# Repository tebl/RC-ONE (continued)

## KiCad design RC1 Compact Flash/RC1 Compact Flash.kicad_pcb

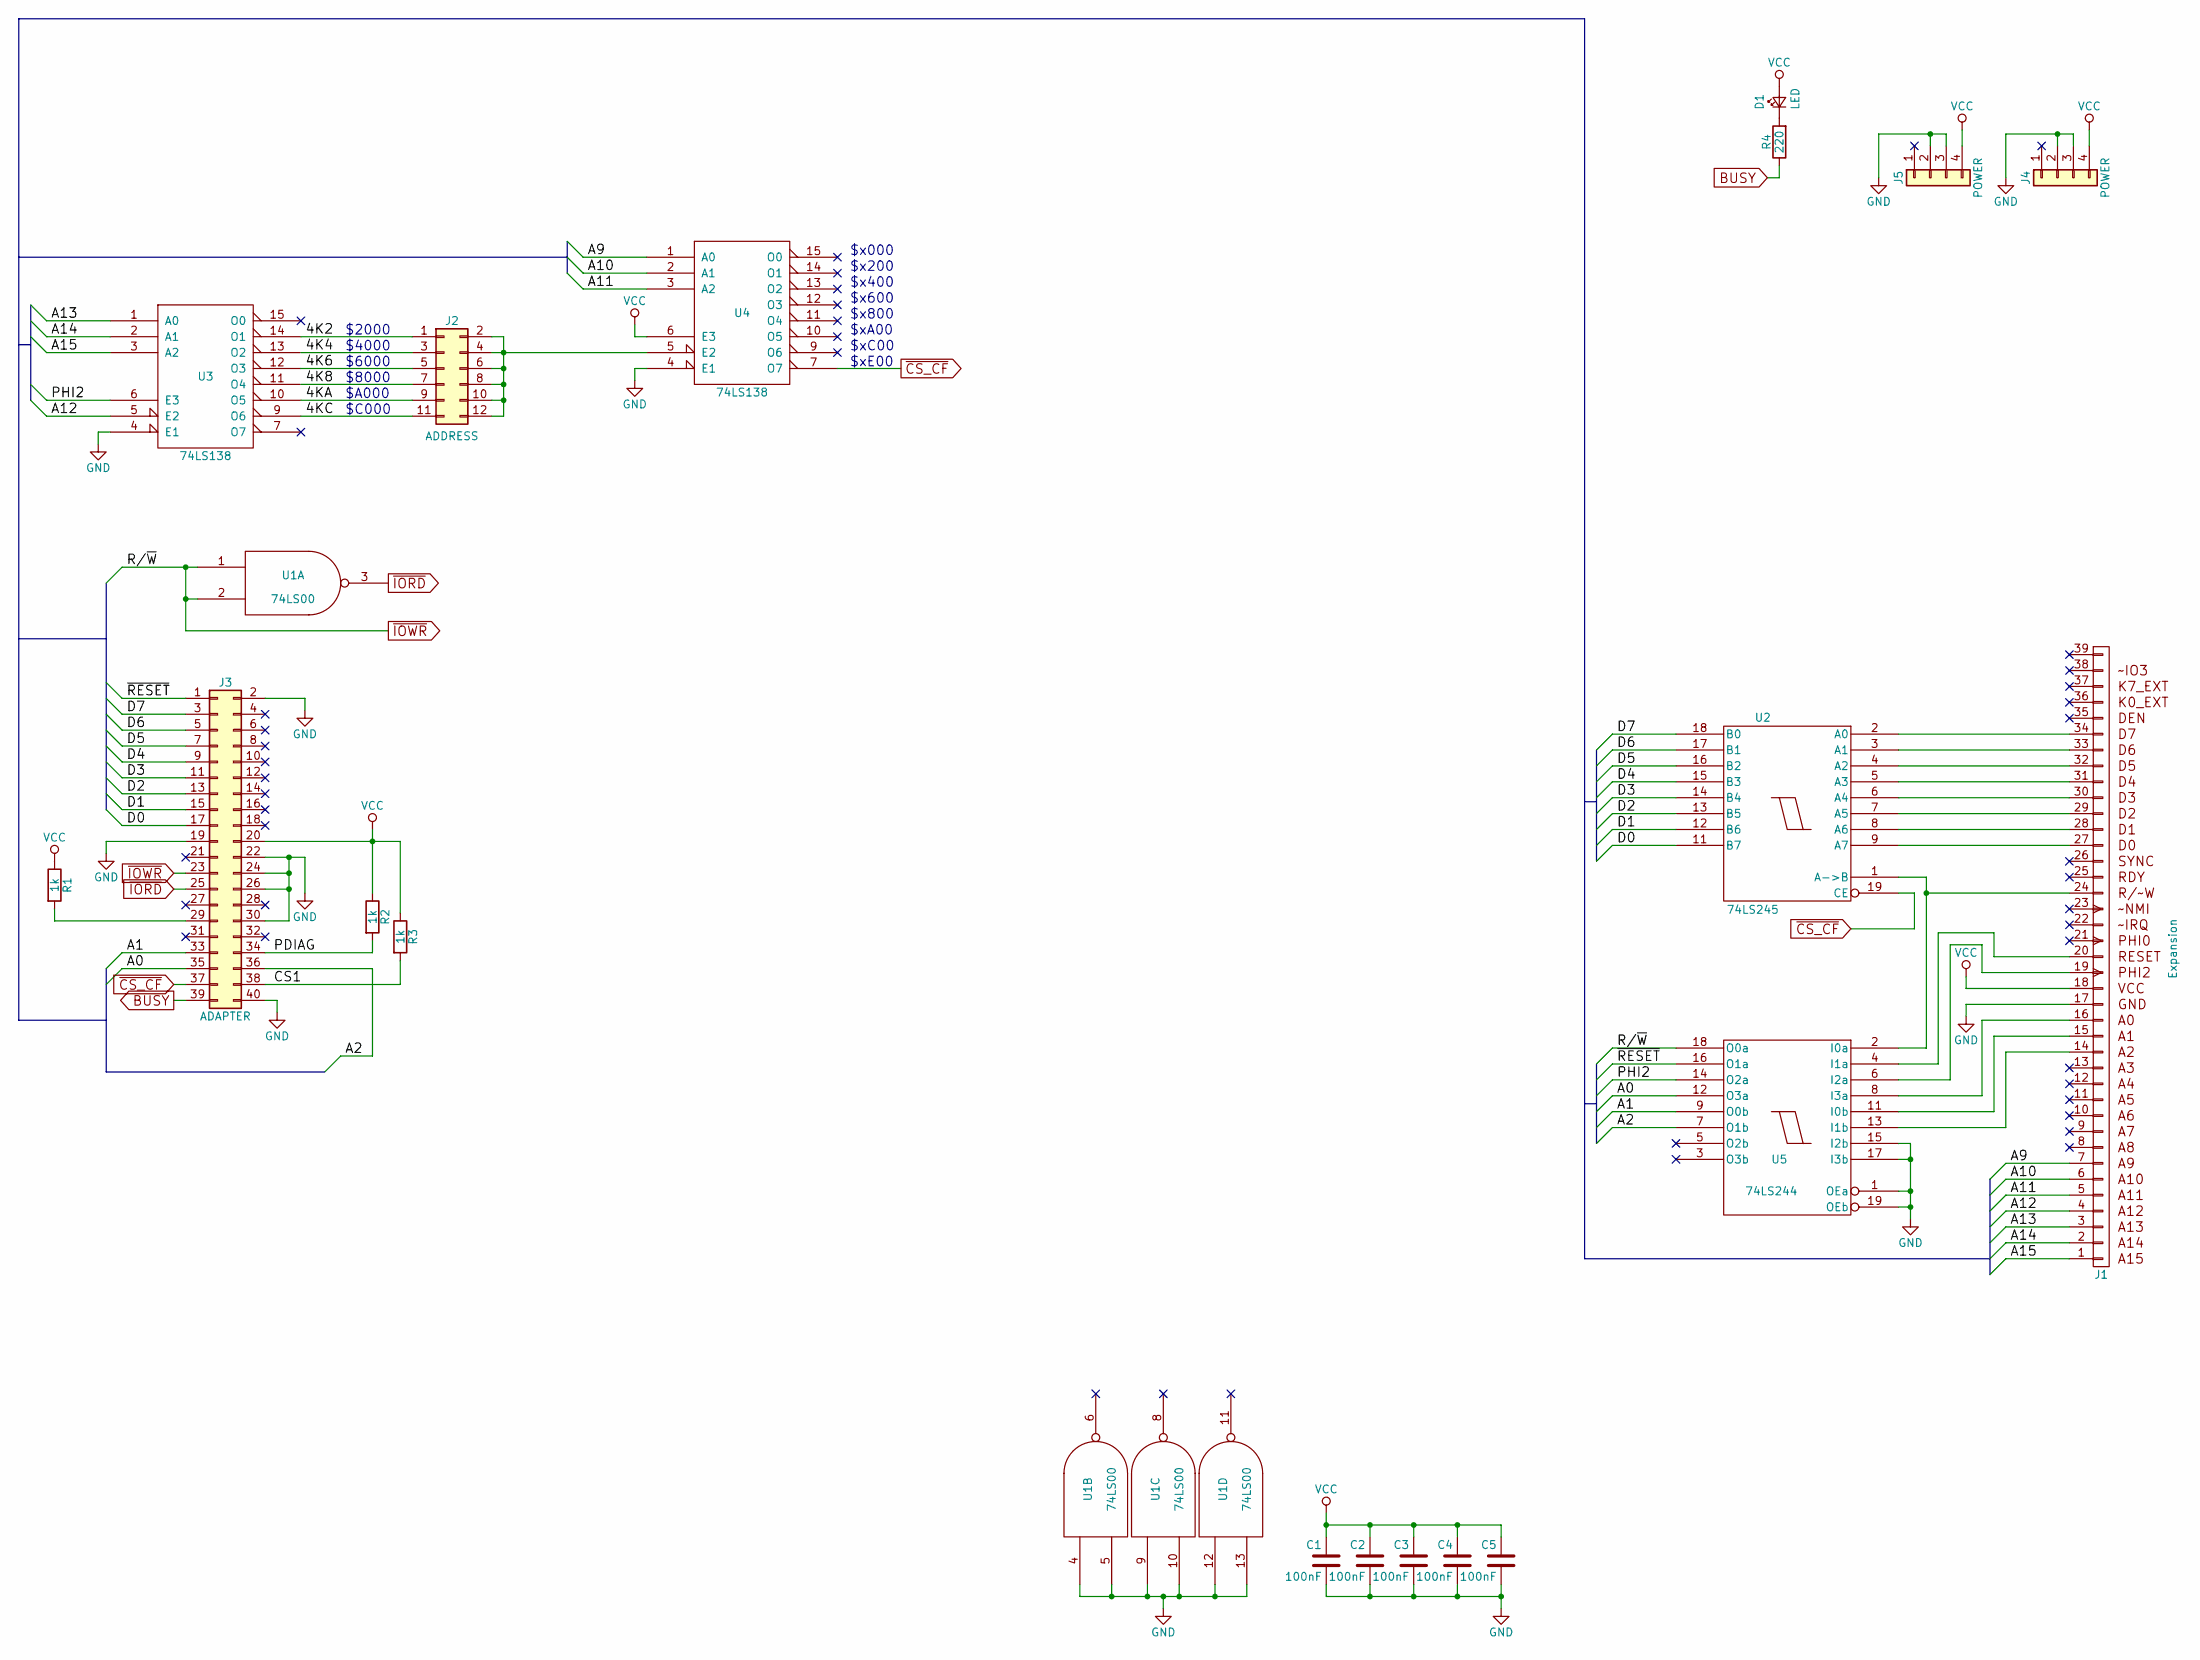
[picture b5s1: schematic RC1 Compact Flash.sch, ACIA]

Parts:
C1, C2, C3, C4, C5: 100nF; C_Disc_D4.7mm_W2.5mm_P5.00mm
D1: LED; LED_D5.0mm_Horizontal_O3.81mm_Z3.0mm
J1: Expansion; Pin_Header_Angled_1x39_Pitch2.54mm
J2: ADDRESS; Pin_Header_Straight_2x06_Pitch2.54mm
J3: ADAPTER; IDC-Header_2x20_P2.54mm_Horizontal
J4, J5: POWER; Pin_Header_Angled_1x04_Pitch2.54mm
R1, R2, R3: 1k; R_Axial_DIN0207_L6.3mm_D2.5mm_P10.16mm_Horizontal
R4: 220; R_Axial_DIN0207_L6.3mm_D2.5mm_P10.16mm_Horizontal
U1: 74LS00; DIP-14_W7.62mm_Socket_LongPads
U2: 74LS245; DIP-20_W7.62mm_Socket_LongPads
U3, U4: 74LS138; DIP-16_W7.62mm_Socket_LongPads
U5: 74LS244; DIP-20_W7.62mm_Socket_LongPads

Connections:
/4K2: J2.1, U3.14 (O1)
/4K4: J2.3, U3.13 (O2)
/4K6: J2.5, U3.12 (O3)
/4K8: J2.7, U3.11 (O4)
/4KA: J2.9, U3.10 (O5)
/4KC: J2.11, U3.9 (O6)
/A0: J3.35, U5.12 (O3a)
/A1: J3.33, U5.9 (O0b)
/A2: J3.36, U5.7 (O1b)
/A9: J1.7 (A9), U4.1 (A0)
/A10: J1.6 (A10), U4.2 (A1)
/A11: J1.5 (A11), U4.3 (A2)
/A12: J1.4 (A12), U3.5 (E2)
/A13: J1.3 (A13), U3.1 (A0)
/A14: J1.2 (A14), U3.2 (A1)
/A15: J1.1 (A15), U3.3 (A2)
/CS1: J3.38, R3.2
/D0: J3.17, U2.11 (B7)
/D1: J3.15, U2.12 (B6)
/D2: J3.13, U2.13 (B5)
/D3: J3.11, U2.14 (B4)
/D4: J3.9, U2.15 (B3)
/D5: J3.7, U2.16 (B2)
/D6: J3.5, U2.17 (B1)
/D7: J3.3, U2.18 (B0)
/PDIAG: J3.34, R2.2
/PHI2: U3.6 (E3), U5.14 (O2a)
/~RESET: J3.1, U5.16 (O1a)
BUSY: J3.39, R4.1
GND: C1.2, C2.2, C3.2, C4.2, C5.2, J1.17, J3.2, J3.19, J3.22, J3.24, J3.26, J3.30, J3.40, J4.2, J4.3, J5.2, J5.3, U1.4, U1.5, U1.7 (GND), U1.9, U1.10, U1.12, U1.13, U2.10 (GND), U3.4 (E1), U3.8 (GND), U4.4 (E1), U4.8 (GND), U5.1 (OEa), U5.10 (GND), U5.15 (I2b), U5.17 (I3b), U5.19 (OEb)
unnamed: D1.1 (K), R4.2
unnamed: J1.14 (A2), U5.13 (I1b)
unnamed: J1.15 (A1), U5.11 (I0b)
unnamed: J1.16 (A0), U5.8 (I3a)
unnamed: J1.19 (PHI2), U5.6 (I2a)
unnamed: J1.20 (RESET), U5.4 (I1a)
unnamed: J1.24 (RW), U2.1 (A->B), U5.2 (I0a)
unnamed: J1.27 (D0), U2.9 (A7)
unnamed: J1.28 (D1), U2.8 (A6)
unnamed: J1.29 (D2), U2.7 (A5)
unnamed: J1.30 (D3), U2.6 (A4)
unnamed: J1.31 (D4), U2.5 (A3)
unnamed: J1.32 (D5), U2.4 (A2)
unnamed: J1.33 (D6), U2.3 (A1)
unnamed: J1.34 (D7), U2.2 (A0)
unnamed: J2.2, J2.4, J2.6, J2.8, J2.10, J2.12, U4.5 (E2)
unnamed: J3.29, R1.2
VCC: C1.1, C2.1, C3.1, C4.1, C5.1, D1.2 (A), J1.18, J3.20, J4.4, J5.4, R1.1, R2.1, R3.1, U1.14 (VCC), U2.20 (VCC), U3.16 (VCC), U4.6 (E3), U4.16 (VCC), U5.20 (VCC)
~CS_CF: J3.37, U2.19 (CE), U4.7 (O7)
~IORD: J3.25, U1.3
~IOWR: J3.23, U1.1, U1.2, U5.18 (O0a)

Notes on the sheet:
$2000
$4000
$6000
$8000
$A000
$C000
$x000
$xE00
$x400
$x200
$x600
$x800
$xC00
$xA00

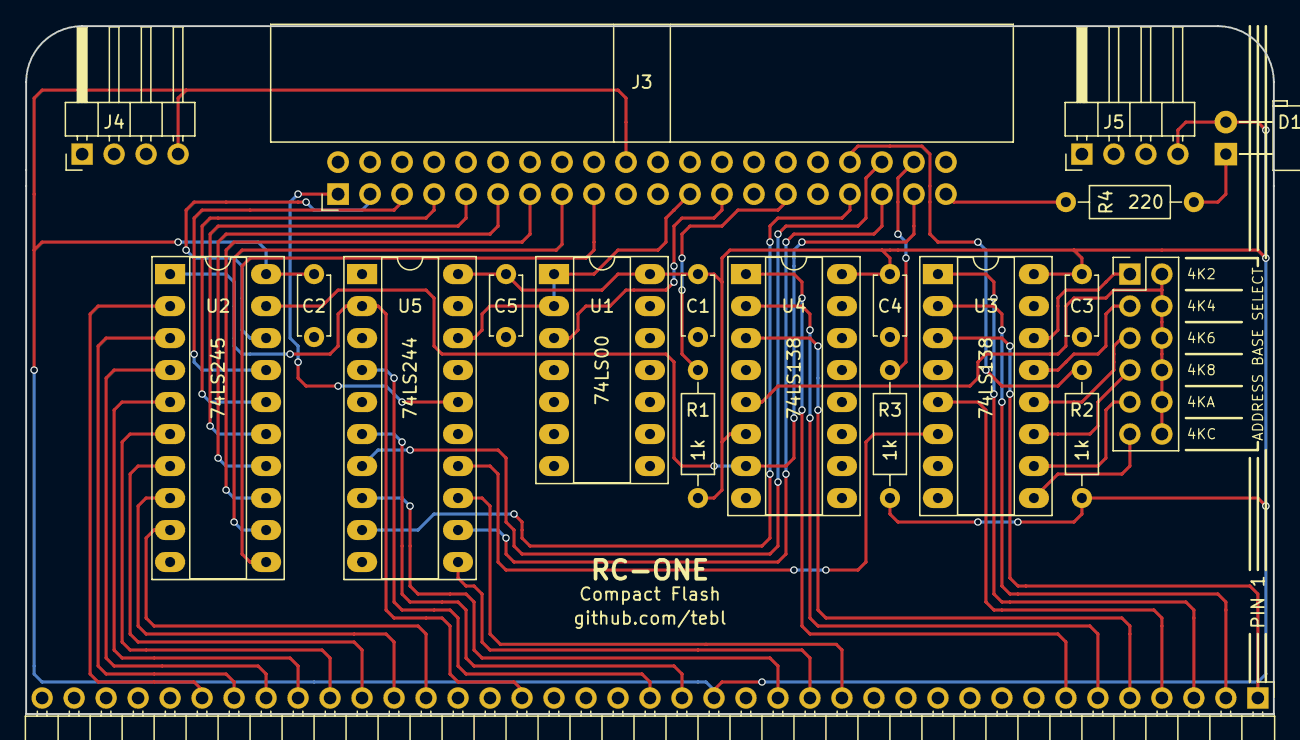
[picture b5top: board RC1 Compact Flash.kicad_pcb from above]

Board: 2 copper layers, 99.1 x 54.6 mm, 20 parts (0 on the bottom side), 51 nets.

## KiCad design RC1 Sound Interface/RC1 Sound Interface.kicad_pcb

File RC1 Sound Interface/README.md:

# RC-ONE Sound Interface (SID)

**This design is untested!**

Made in order to use Commodore 64 SID chip replacements such as the SwinSID, armSID or fpgaSID as a sound device. Purposefully does not include the extra voltages needed to use a real SID-chip, mostly because the functioning chips that are left in this world belong in real computers (also, did not want to mess around with more than one power rail).

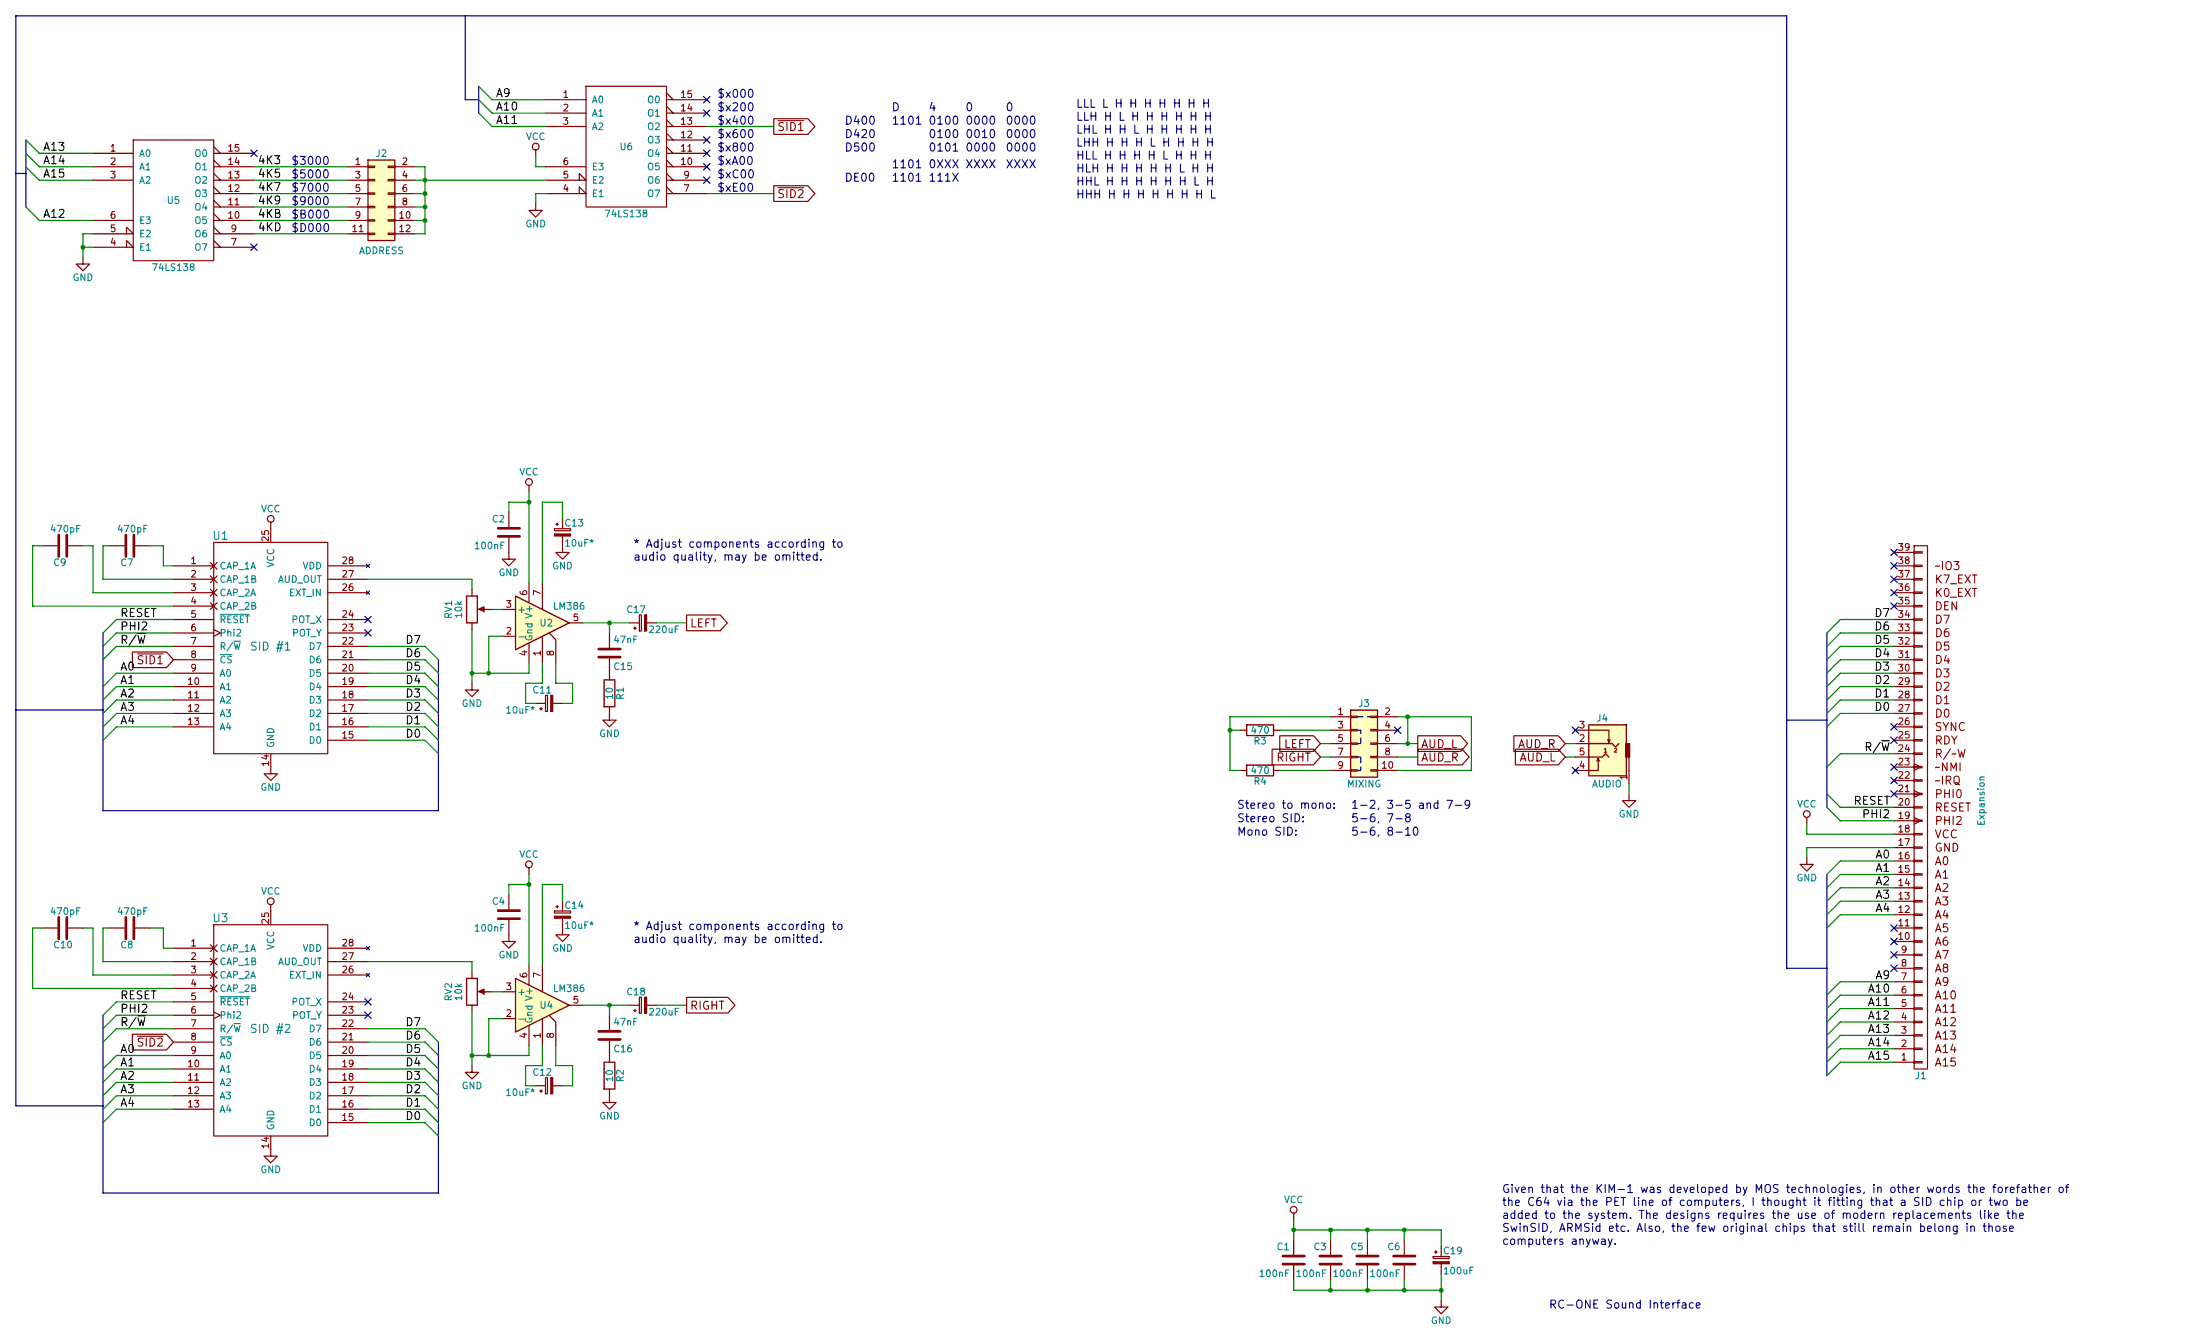
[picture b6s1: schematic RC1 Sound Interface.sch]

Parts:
C1, C2, C3, C4, C5, C6: 100nF; C_Disc_D4.7mm_W2.5mm_P5.00mm
C7, C8, C9, C10: 470pF; C_Disc_D4.7mm_W2.5mm_P5.00mm
C11, C12, C13, C14: 10uF*; CP_Radial_D5.0mm_P2.50mm
C15, C16: 47nF; C_Disc_D4.7mm_W2.5mm_P5.00mm
C17, C18: 220uF; CP_Radial_D5.0mm_P2.50mm
C19: 100uF; CP_Radial_D5.0mm_P2.50mm
J1: Expansion; Pin_Header_Angled_1x39_Pitch2.54mm
J2: ADDRESS; Pin_Header_Straight_2x06_Pitch2.54mm
J3: MIXING; Pin_Header_Straight_2x05_Pitch2.54mm
J4: AUDIO; Tayda_3.5mm_stereo_TRS_jack_A-853
R1, R2: 10; R_Axial_DIN0207_L6.3mm_D2.5mm_P10.16mm_Horizontal
R3, R4: 470; R_Axial_DIN0207_L6.3mm_D2.5mm_P10.16mm_Horizontal
RV1, RV2: 10k; Potentiometer_Trimmer_Bourns_3296W
U1: SID #1; DIP-28_W15.24mm_Socket
U2, U4: LM386; DIP-8_W7.62mm_Socket
U3: SID #2; DIP-28_W15.24mm_Socket
U5, U6: 74LS138; DIP-16_W7.62mm_Socket

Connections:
/4K3: J2.1, U5.14 (O1)
/4K5: J2.3, U5.13 (O2)
/4K7: J2.5, U5.12 (O3)
/4K9: J2.7, U5.11 (O4)
/4KB: J2.9, U5.10 (O5)
/4KD: J2.11, U5.9 (O6)
/A0: J1.16 (A0), U1.9 (A0), U3.9 (A0)
/A1: J1.15 (A1), U1.10 (A1), U3.10 (A1)
/A2: J1.14 (A2), U1.11 (A2), U3.11 (A2)
/A3: J1.13 (A3), U1.12 (A3), U3.12 (A3)
/A4: J1.12 (A4), U1.13 (A4), U3.13 (A4)
/A9: J1.7 (A9), U6.1 (A0)
/A10: J1.6 (A10), U6.2 (A1)
/A11: J1.5 (A11), U6.3 (A2)
/A12: J1.4 (A12), U5.6 (E3)
/A13: J1.3 (A13), U5.1 (A0)
/A14: J1.2 (A14), U5.2 (A1)
/A15: J1.1 (A15), U5.3 (A2)
/D0: J1.27 (D0), U1.15 (D0), U3.15 (D0)
/D1: J1.28 (D1), U1.16 (D1), U3.16 (D1)
/D2: J1.29 (D2), U1.17 (D2), U3.17 (D2)
/D3: J1.30 (D3), U1.18 (D3), U3.18 (D3)
/D4: J1.31 (D4), U1.19 (D4), U3.19 (D4)
/D5: J1.32 (D5), U1.20 (D5), U3.20 (D5)
/D6: J1.33 (D6), U1.21 (D6), U3.21 (D6)
/D7: J1.34 (D7), U1.22 (D7), U3.22 (D7)
/PHI2: J1.19 (PHI2), U1.6 (Phi2), U3.6 (Phi2)
/R/~W: J1.24 (RW), U1.7 (R/~W), U3.7 (R/~W)
/RESET: J1.20 (RESET), U1.5 (~RESET), U3.5 (~RESET)
AUD_L: J3.2, J3.6, J3.10, J4.5
AUD_R: J3.8, J4.2
GND: C1.2, C2.2, C3.2, C4.2, C5.2, C6.2, C13.2, C14.2, C19.2, J1.17, J4.1, R1.2, R2.2, RV1.3, RV2.3, U1.14 (GND), U2.2 (-), U2.4 (Gnd), U3.14 (GND), U4.2 (-), U4.4 (Gnd), U5.4 (E1), U5.5 (E2), U5.8 (GND), U6.4 (E1), U6.8 (GND)
LEFT: C17.2, J3.5
unnamed: C7.1, U1.1 (CAP_1A)
unnamed: C7.2, U1.2 (CAP_1B)
unnamed: C8.1, U3.1 (CAP_1A)
unnamed: C8.2, U3.2 (CAP_1B)
unnamed: C9.1, U1.3 (CAP_2A)
unnamed: C9.2, U1.4 (CAP_2B)
unnamed: C10.1, U3.3 (CAP_2A)
unnamed: C10.2, U3.4 (CAP_2B)
unnamed: C11.1, U2.1
unnamed: C11.2, U2.8
unnamed: C12.1, U4.1
unnamed: C12.2, U4.8
unnamed: C13.1, U2.7
unnamed: C14.1, U4.7
unnamed: C15.1, R1.1
unnamed: C15.2, C17.1, U2.5
unnamed: C16.1, R2.1
unnamed: C16.2, C18.1, U4.5
unnamed: J2.2, J2.4, J2.6, J2.8, J2.10, J2.12, U6.5 (E2)
unnamed: J3.1, R3.2, R4.2
unnamed: J3.3, R3.1
unnamed: J3.9, R4.1
unnamed: RV1.1, U1.27 (AUD_OUT)
unnamed: RV1.2, U2.3 (+)
unnamed: RV2.1, U3.27 (AUD_OUT)
unnamed: RV2.2, U4.3 (+)
RIGHT: C18.2, J3.7
VCC: C1.1, C2.1, C3.1, C4.1, C5.1, C6.1, C19.1, J1.18, U1.25 (VCC), U2.6 (V+), U3.25 (VCC), U4.6 (V+), U5.16 (VCC), U6.6 (E3), U6.16 (VCC)
~SID1: U1.8 (~CS), U6.13 (O2)
~SID2: U3.8 (~CS), U6.7 (O7)

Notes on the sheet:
RC-ONE Sound Interface
$3000
$5000
$7000
$9000
$B000
$D000
Given that the KIM-1 was developed by MOS technologies, in other words the forefather of the C64 via the PET line of computers, I thought it fitting that a SID chip or two be added to the system. The designs requires the use of modern replacements like the SwinSID, ARMSid etc. Also, the few origina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
$x000
$xE00
1101
0100
0010
0000
0101
D420
D400
D500
LLL L H H H H H H H LLH H L H H H H H H LHL H H L H H H H H LHH H H H L H H H H HLL H H H H L H H H HLH H H H H H L H H HHL H H H H H H L H HHH H H H H H H H L
0XXX
XXXX
DE00
111X
$x400
$x200
$x600
$x800
$xC00
$xA00
1-2, 3-5 and 7-9
Stereo to mono:
Stereo SID:
5-6, 7-8
Mono SID:
5-6, 8-10
* Adjust components according to audio quality, may be omitted.

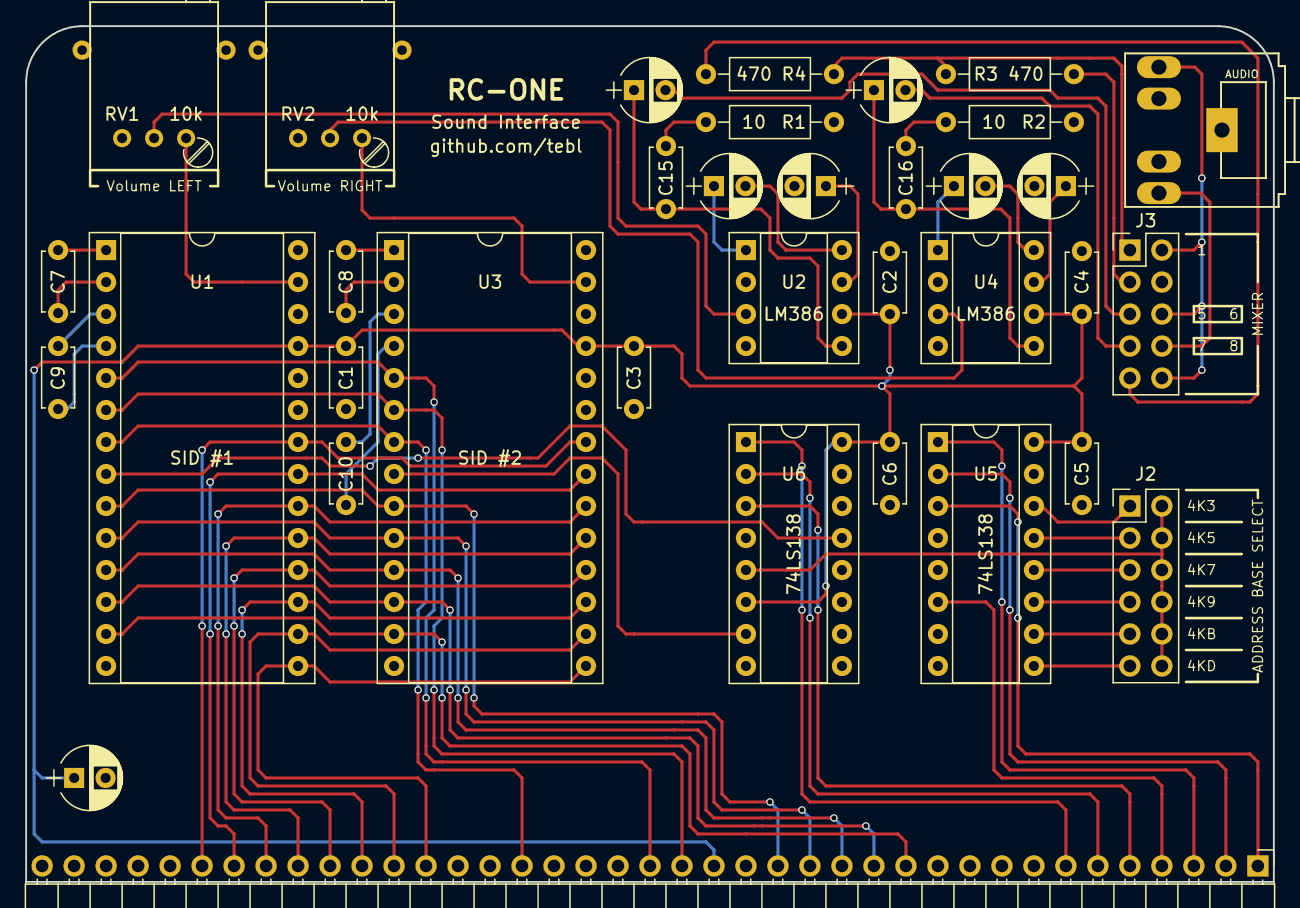
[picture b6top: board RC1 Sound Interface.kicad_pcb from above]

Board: 2 copper layers, 99.1 x 67.9 mm, 35 parts (0 on the bottom side), 63 nets.

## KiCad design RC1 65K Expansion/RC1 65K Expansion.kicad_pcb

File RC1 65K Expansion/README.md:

# RC-ONE

Among the years I've built quite a few computers, some bought as kits from various vendors and some I even designed myself based on available designs describes in books and other technical resources - above all, there was one I really wanted above all of them; the KIM-1! The [RC-ONE](https://github.com/tebl/RC-ONE) is a functional replica designed in a modular fashion, for the specifics seaddresse specific module.

## 65K Expansion
The original KIM-1 computer as well as RC-ONE base system only has around 1K of RAM available as well as 2K of ROM, it also limits the entire address space available to the 6502 CPU to 8K where most of it has already been taken up. The RC-ONE by comparison uses the same address decoding scheme, but actually has 32K of RAM and 8K of ROM on the base system, most of it simply isn't accessible by the base system. The addition of the 65K Expansion allows the computer to access up to 29K of RAM , the full 8K of ROM as well as increases the total address space to the 64K limit set by the 6502 processor.

For a complete overview of the addressing used with the computer, see [Memory Map](https://github.com/tebl/RC-ONE/raw/master/documentation/memory_map.pdf) ([ODS-format](https://github.com/tebl/RC-ONE/raw/master/documentation/memory_map.ods)) for a comparison between the relevant systems - preview of the main bits below as well!

The 65K Expansion expands upon the address decoding performed by the [CPU-board](https://github.com/tebl/RC-ONE/tree/master/RC1%20CPU) so that more of the address space is both freed up, my implementation on it is for the most part functionally the same as the one described in the [KIM-1 Programming Manual](http://users.telenet.be/kim1-6502/6502/proman.html) (which is why it's called the *65K Expansion*).

Given that since the 65K Expansion changes the address decoding, the *DEN* jumper on the CPU module needs to be removed in order for the computer to function with the 65K Expansion taking over the heavy lifting on the address decoding. Likewise, the *RAM_EXT* and *ROM_EXT* configuration must be changed so that pins 2-3 on them are jumpered in order for the additional RAM and ROM to be accessible.

The original KIM-1 computer came with two 6530s, one dedicated to the user interface and the other available to do with as you please. The RC-ONE base system only has the one 6532 replacing the former, the latter has been added to the 65K Expansion so that you don't have to go without it if you don't actually want to! Quite a lot of the books written for the KIM-1 depend on the additional I/O lines in order to control fun little hardware experiments and I think it's worth getting the extra 6532 for this purpuse.

## Configuration
| Reference  | Position | Description                                              |
| ---------- | -------- | -------------------------------------------------------- |
| DEN     *  | o o **   | **Remove** jumper when using 65K Expansion               |
| RAM_EXT *  | 1-2      | Jumper when **NOT** using with 65K Expansion             |
|            | 2-3 **   | RAM decoding performed by 65K Expansion                  |
| ROM_EXT *  | 1-2      | Jumper when **NOT** using with 65K Expansion             |
|            | 2-3 **   | ROM decoding performed by 65K Expansion                  |
| LOW MEMORY | 1-2      | 1K low memory size ($0000 - $03FF)                       |
|            | 3-4      | 2K low memory size ($0000 - $07FF)                       |
|            | 5-6      | 4K low memory size ($0000 - $0FFF)                       |
|            | 7-8 **   | 5K low memory size ($0000 - $13FF)                       |
| RAM_8K1    | o o      | Enable 8K RAM size ($2000 - $3FFF)                       |
| RAM_8K2    | o o      | Enable 8K RAM ($4000 - $5FFF)                            |
| RAM_8K3    | o o      | Enable 8K RAM ($6000 - $7FFF)                            |
| RIOT_IO3   | 1-2 **   | Enable RIOT chip                                         |
|            | 2-3      | RIOT chip disabled                                       |
| RIOT_IRQ   | 1-2      | RIOT chip IRQ line connected to BUS                      |
|            | 2-3 **   | RIOT chip IRQ line not connected                         |
| RIOT_A4    | 1-2 **   | Invert A4 to match 6532 registers to 6530                |
|            | 2-3      | 6532 registers according to 6532 datasheet               |

*) These jumpers are found on the CPU board
**) Marks the default jumpered positions for a RC-ONE system, but mostly these are suggestions meant to get you started with a computer functionally equivalent to a 65K expanded KIM-1 with a 4K RAM expansion installed.

## Connectors
The following additional headers break out additional signals. *EXTRA* and *K1-K4* allows a convenient hookup point for decoded memory segments for use in other projects as they don't conflict with any other expansions present on the same backplane (pin 1 is on the top). Application I/O is numbered odd-even, see reverse side of PCB or this [image](https://github.com/tebl/RC-ONE/raw/master/RC1%2065K%20Expansion/gallery/application_io.png) for reference.

| Reference       | Pins              | Description                                              |
| --------------- | ----------------- | -------------------------------------------------------- |
| Application I/O | 1 (bottom left)   | GND                                                      |
|                 | 2 (top left)      | GND                                                      |
|                 | 3                 | PB7                                                      |
|                 | 4                 | PA7                                                      |
|                 | 5                 | PB6                                                      |
|                 | 6                 | PA6                                                      |
|                 | 7                 | PB5                                                      |
|                 | 8                 | PA5                                                      |
|                 | 9                 | PB4                                                      |
|                 | 10                | PA4                                                      |
|                 | 11                | PB3                                                      |
|                 | 12                | PA3                                                      |
|                 | 13                | PB2                                                      |
|                 | 14                | PA2                                                      |
|                 | 15                | PB1                                                      |
|                 | 16                | PA1                                                      |
|                 | 17                | PB0                                                      |
|                 | 18                | PA0                                                      |
|                 | 19 (bottom right) | GND                                                      |
|                 | 20 (top right)    | VCC                                                      |
| EXTRA           | 1 (top)           | 8K4    ($8000 - $9FFF)                                   |
|                 | 2                 | 8K5    ($A000 - $BFFF)                                   |
|                 | 3                 | 8K6    ($C000 - $DFFF)                                   |
| K1-K4           | 1 (top)           | 8K0 K1 ($0400 - $07FF)                                   |
|                 | 2                 | 8K0 K2 ($0800 - $0BFF)                                   |
|                 | 3                 | 8K0 K3 ($0C00 - $0FFF)                                   |
|                 | 4                 | 8K0 K4 ($1000 - $13FF)                                   |

# Schematic
The supplied KiCad files should be sufficient as both a schematic and as a starting point for ordering PCBs (basically you could just zip the contents of the export folder and upload that on a fabrication site), the schematic is also available in [PDF-format](https://github.com/tebl/RC-ONE/raw/master/RC1%20Keypad%20MX/export/RC1%20Keypad%20MX.pdf) so that you print it out and hang it on your office wall, excellent conversation starter at any technology-oriented business worth working at (or so I keep telling myself)!

# BOM
This is the part list as it stands now, most should be easy to get a hold of from your local electronic component shop though you might have to consider other sources depending on the quality of your local vendor.

| Reference          | Item                                     | Count |
| ------------------ | ---------------------------------------- | ----- |
| PCB                | Fabricate yourself using Gerber files    |     1 |
| D1                 | 5mm LED                                  |     1 |
| J1                 | 2x8 straight pin header                  |     1 |
| SW1-SW22,SW23,SW24 | 3 or 5 pin Cherry MX key switches *      |    23 |
| SST                | 1-position DIP switch                    |     1 |
| Keycaps            | Blank 1U keycaps **                      |    23 |
| Keypad cable       | 2x8 pin JTAG cable                       |     1 |

*) Any type of Cherry MX compatible switches can be used, these can be either of the 3 or pin variety. Personally I bought the green Gateron MX switches and they work great though you'd probably want to buy the non-green version if you don't like the clicky sound.

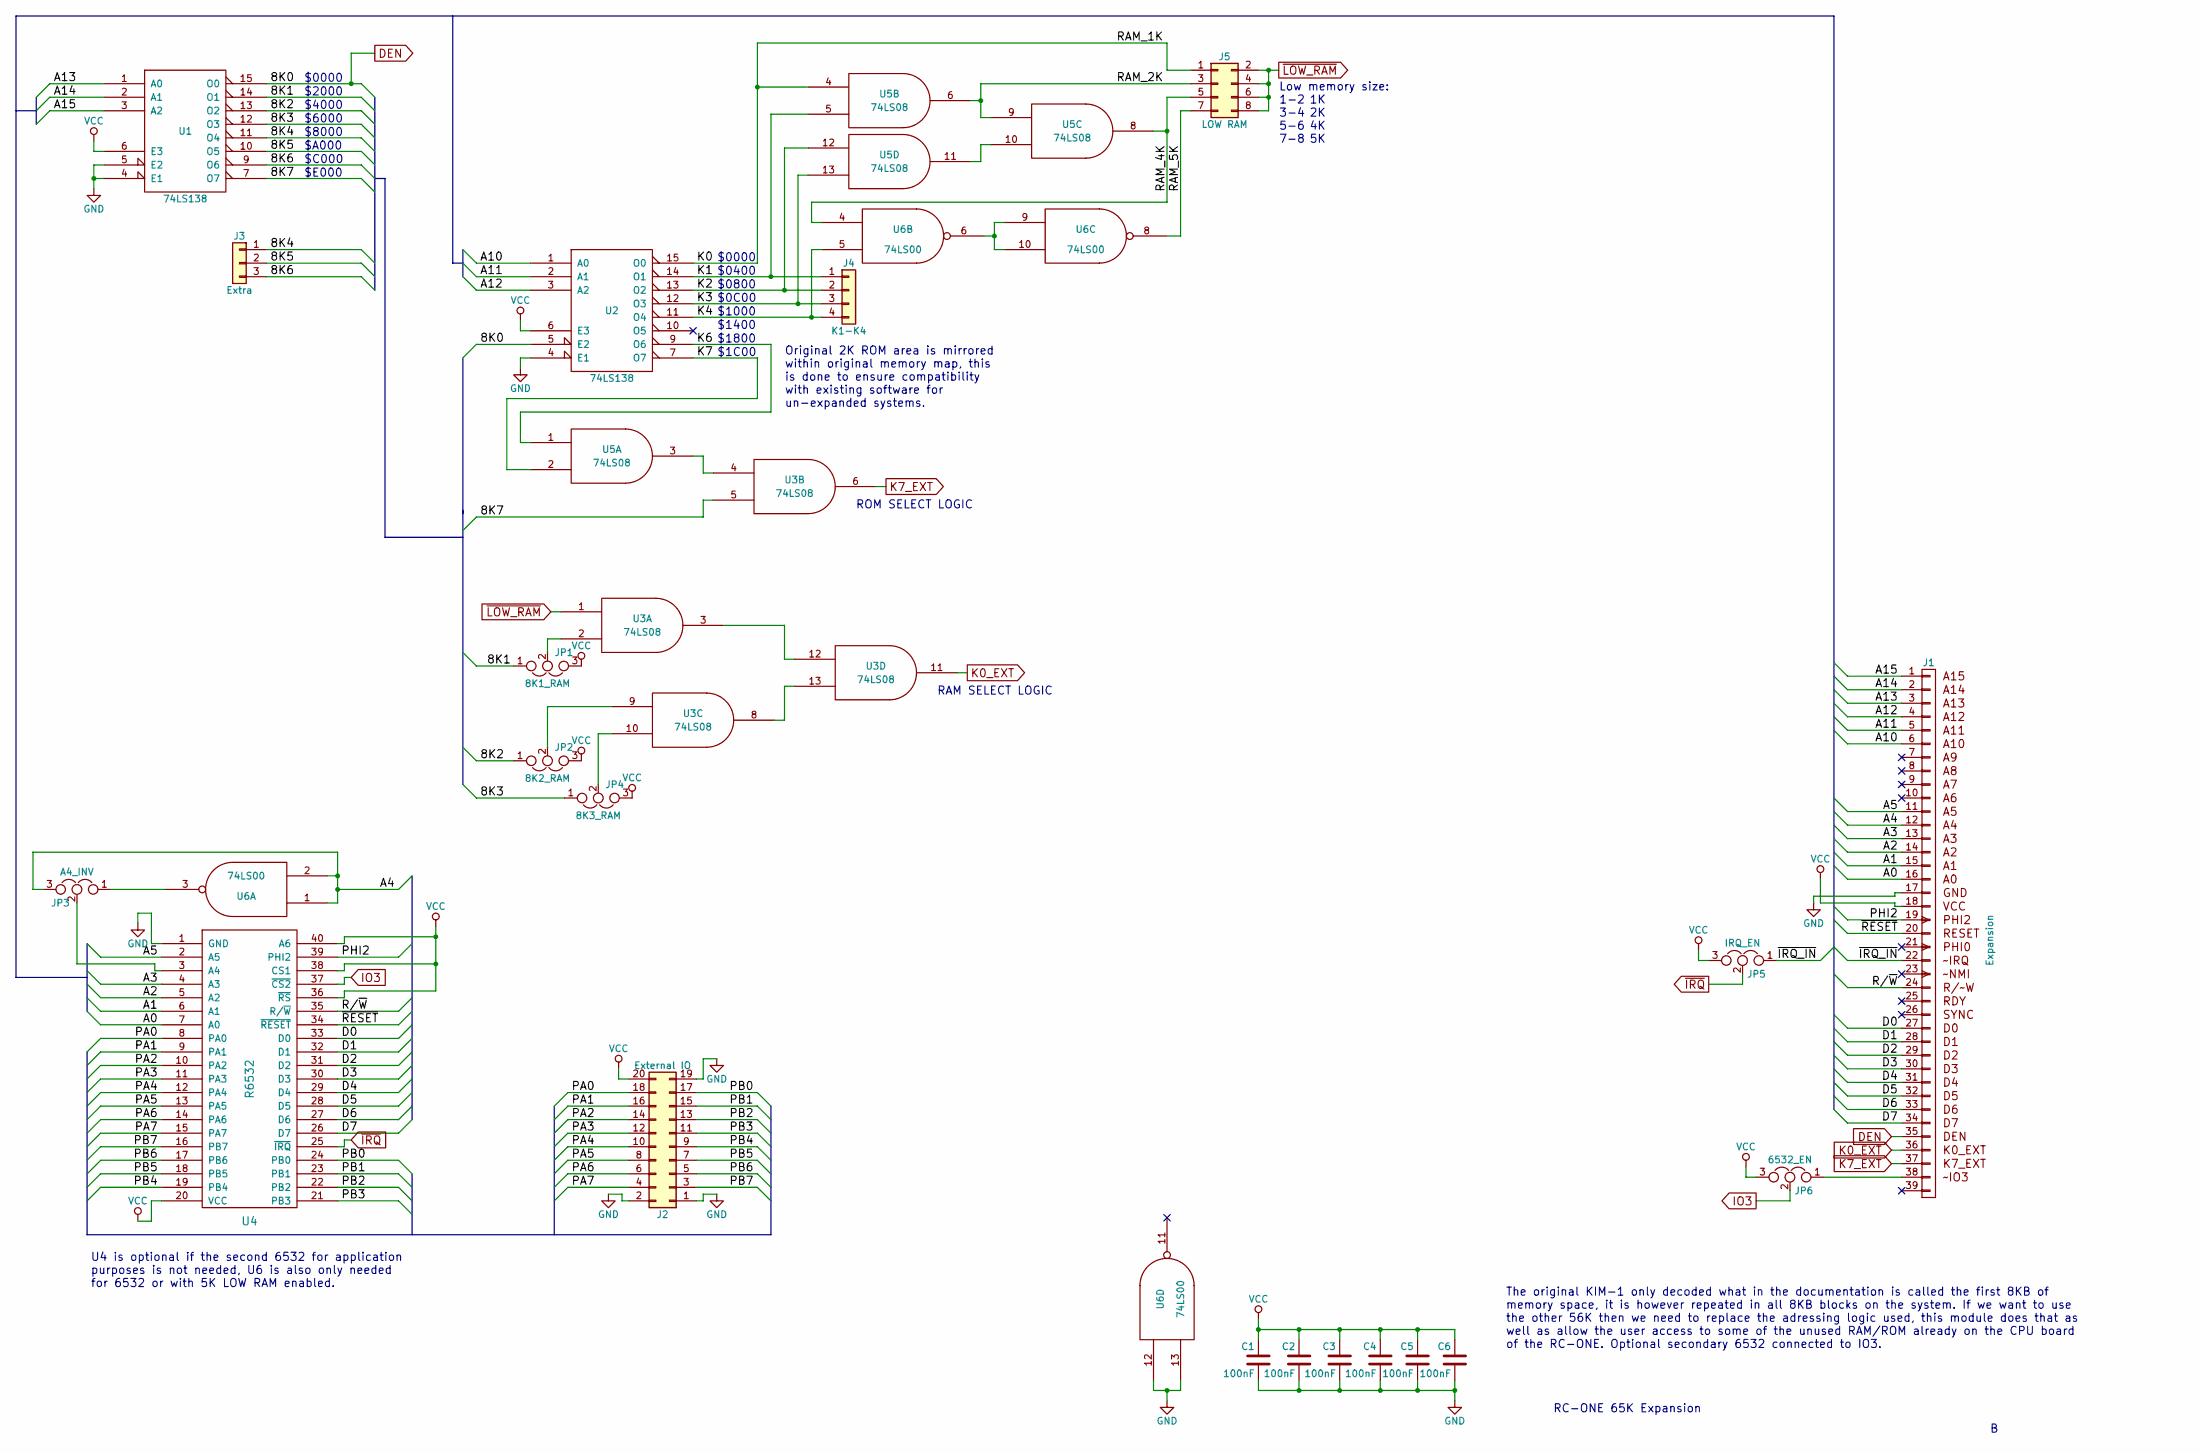
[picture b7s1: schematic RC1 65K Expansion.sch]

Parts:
C1, C2, C3, C4, C5, C6: 100nF; C_Disc_D4.7mm_W2.5mm_P5.00mm
J1: Expansion; Pin_Header_Angled_1x39_Pitch2.54mm
J2: External IO; Pin_Header_Straight_2x10_Pitch2.54mm
J3: Extra; Pin_Header_Straight_1x03_Pitch2.54mm
J4: K1-K4; Pin_Header_Straight_1x04_Pitch2.54mm
J5: LOW RAM; Pin_Header_Straight_2x04_Pitch2.54mm
JP1: 8K1_RAM; Pin_Header_Straight_1x03_Pitch2.54mm
JP2: 8K2_RAM; Pin_Header_Straight_1x03_Pitch2.54mm
JP3: A4_INV; Pin_Header_Straight_1x03_Pitch2.54mm
JP4: 8K3_RAM; Pin_Header_Straight_1x03_Pitch2.54mm
JP5: IRQ_EN; Pin_Header_Straight_1x03_Pitch2.54mm
JP6: 6532_EN; Pin_Header_Straight_1x03_Pitch2.54mm
U1, U2: 74LS138; DIP-16_W7.62mm_Socket
U3, U5: 74LS08; DIP-14_W7.62mm_Socket
U4: R6532; DIP-40_W15.24mm_Socket
U6: 74LS00; DIP-14_W7.62mm_Socket

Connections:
/8K1: JP1.1, U1.14 (O1)
/8K2: JP2.1, U1.13 (O2)
/8K3: JP4.1, U1.12 (O3)
/8K4: J3.1, U1.11 (O4)
/8K5: J3.2, U1.10 (O5)
/8K6: J3.3, U1.9 (O6)
/8K7: U1.7 (O7), U3.5
/A0: J1.16 (A0), U4.7 (A0)
/A1: J1.15 (A1), U4.6 (A1)
/A2: J1.14 (A2), U4.5 (A2)
/A3: J1.13 (A3), U4.4 (A3)
/A4: J1.12 (A4), JP3.3, U6.1, U6.2
/A5: J1.11 (A5), U4.2 (A5)
/A10: J1.6 (A10), U2.1 (A0)
/A11: J1.5 (A11), U2.2 (A1)
/A12: J1.4 (A12), U2.3 (A2)
/A13: J1.3 (A13), U1.1 (A0)
/A14: J1.2 (A14), U1.2 (A1)
/A15: J1.1 (A15), U1.3 (A2)
/D0: J1.27 (D0), U4.33 (D0)
/D1: J1.28 (D1), U4.32 (D1)
/D2: J1.29 (D2), U4.31 (D2)
/D3: J1.30 (D3), U4.30 (D3)
/D4: J1.31 (D4), U4.29 (D4)
/D5: J1.32 (D5), U4.28 (D5)
/D6: J1.33 (D6), U4.27 (D6)
/D7: J1.34 (D7), U4.26 (D7)
/K0: J5.1, U2.15 (O0), U5.4
/K1: J4.1, U2.14 (O1), U5.5
/K2: J4.2, U2.13 (O2), U5.12
/K3: J4.3, U2.12 (O3), U5.13
/K4: J4.4, U2.11 (O4), U6.5
/K6: U2.9 (O6), U5.1
/K7: U2.7 (O7), U5.2
/PA0: J2.18, U4.8 (PA0)
/PA1: J2.16, U4.9 (PA1)
/PA2: J2.14, U4.10 (PA2)
/PA3: J2.12, U4.11 (PA3)
/PA4: J2.10, U4.12 (PA4)
/PA5: J2.8, U4.13 (PA5)
/PA6: J2.6, U4.14 (PA6)
/PA7: J2.4, U4.15 (PA7)
/PB0: J2.17, U4.24 (PB0)
/PB1: J2.15, U4.23 (PB1)
/PB2: J2.13, U4.22 (PB2)
/PB3: J2.11, U4.21 (PB3)
/PB4: J2.9, U4.19 (PB4)
/PB5: J2.7, U4.18 (PB5)
/PB6: J2.5, U4.17 (PB6)
/PB7: J2.3, U4.16 (PB7)
/PHI2: J1.19 (PHI2), U4.39 (PHI2)
/R/~W: J1.24 (RW), U4.35 (R/~W)
/RAM_2K: J5.3, U5.6, U5.9
/RAM_4K: J5.5, U5.8, U6.4
/RAM_5K: J5.7, U6.8
/~IRQ_IN: J1.22 (IRQ), JP5.1
/~RESET: J1.20 (RESET), U4.34 (~RESET)
DEN: J1.35 (TX), U1.15 (O0), U2.5 (E2)
GND: C1.2, C2.2, C3.2, C4.2, C5.2, C6.2, J1.17, J2.1, J2.2, J2.19, U1.4 (E1), U1.5 (E2), U1.8 (GND), U2.4 (E1), U2.8 (GND), U3.7 (GND), U4.1 (GND), U5.7 (GND), U6.7 (GND), U6.12, U6.13
IO3: JP6.2, U4.37 (~CS2)
K0_EXT: J1.36 (RX), U3.11
K7_EXT: J1.37 (NMI), U3.6
unnamed: J1.38, JP6.1
unnamed: JP1.2, U3.2
unnamed: JP2.2, U3.9
unnamed: JP3.1, U6.3
unnamed: JP3.2, U4.3 (A4)
unnamed: JP4.2, U3.10
unnamed: U3.4, U5.3
unnamed: U3.3, U3.12
unnamed: U3.8, U3.13
unnamed: U5.10, U5.11
unnamed: U6.6, U6.9, U6.10
VCC: C1.1, C2.1, C3.1, C4.1, C5.1, C6.1, J1.18, J2.20, JP1.3, JP2.3, JP4.3, JP5.3, JP6.3, U1.6 (E3), U1.16 (VCC), U2.6 (E3), U2.16 (VCC), U3.14 (VCC), U4.20 (VCC), U4.36 (~RS), U4.38 (CS1), U4.40 (A6), U5.14 (VCC), U6.14 (VCC)
~IRQ: JP5.2, U4.25 (~IRQ)
~LOW_RAM: J5.2, J5.4, J5.6, J5.8, U3.1

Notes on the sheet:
RC-ONE 65K Expansion
The original KIM-1 only decoded what in the documentation is called the first 8KB of memory space, it is however repeated in all 8KB blocks on the system. If we want to use the other 56K then we need to replace the adressing logic used, this module does that as well as allow the user access to some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
$E000
$0000
$2000
$4000
$6000
$8000
$A000
$C000
RAM SELECT LOGIC
$0400
$0800
$0C00
$1000
$1400
$1800
$1C00
ROM SELECT LOGIC
Low memory size: 1-2 3-4 5-6 7-8
1K 2K 4K 5K
Original 2K ROM area is mirrored within original memory map, this is done to ensure compatibility with existing software for un-expanded systems.
U4 is optional if the second 6532 for application purposes is not needed, U6 is also only needed for 6532 or with 5K LOW RAM enabled.

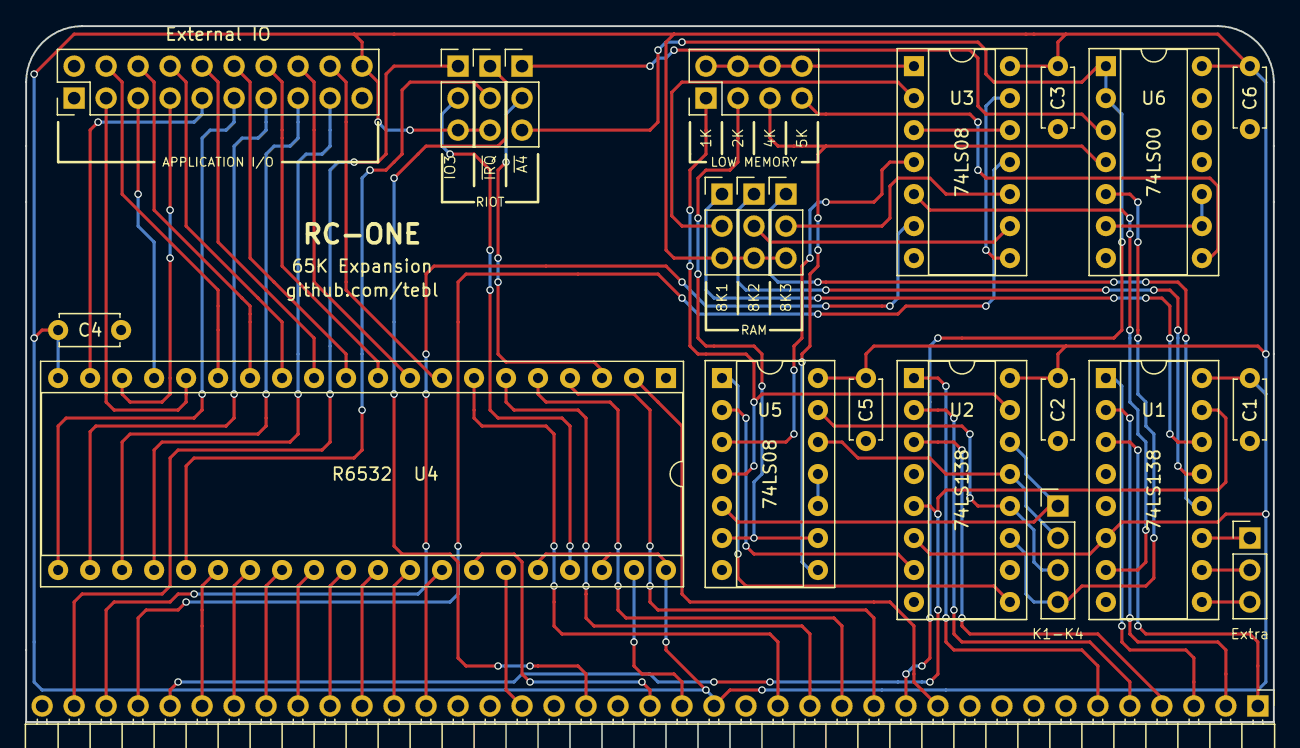
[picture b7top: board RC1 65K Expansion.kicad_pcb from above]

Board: 2 copper layers, 99.1 x 55.2 mm, 23 parts (0 on the bottom side), 76 nets.
